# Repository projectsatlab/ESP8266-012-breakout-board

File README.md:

ESP8266-012F breakout board for sensors and probes devices

Coming soon...

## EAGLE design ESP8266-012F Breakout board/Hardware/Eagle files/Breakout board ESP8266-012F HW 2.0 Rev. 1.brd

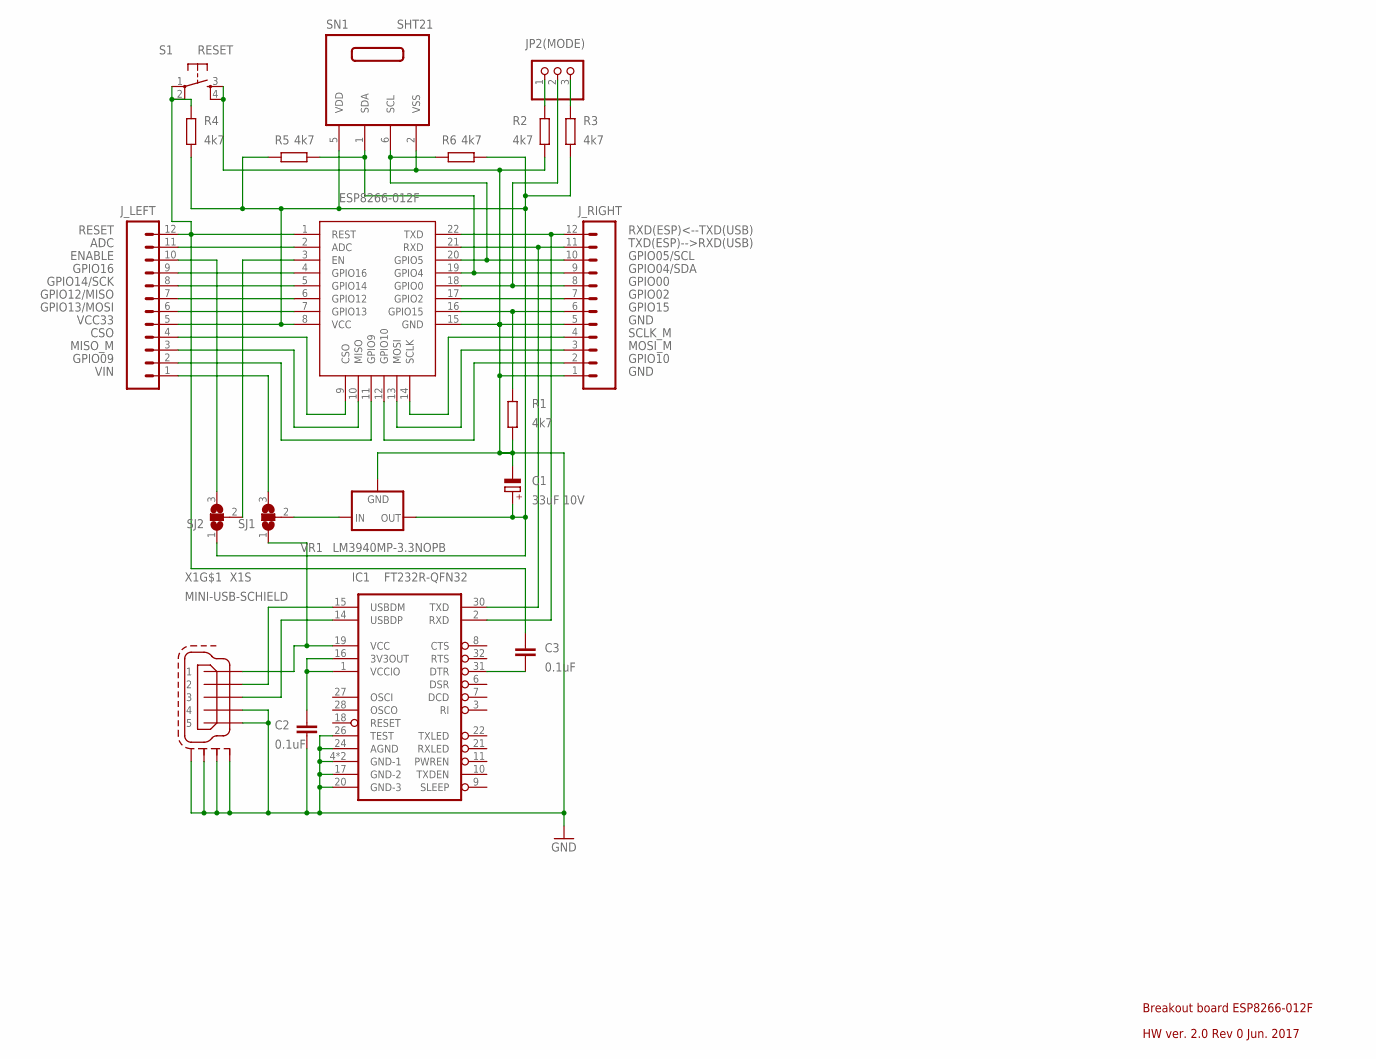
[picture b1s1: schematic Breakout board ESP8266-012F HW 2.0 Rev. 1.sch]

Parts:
C1: 33uF 10V; UD-5X5,8_NICHICON
C2, C3: 0.1uF; C0805
IC1: FT232R-QFN32; QFN32
JP2(MODE): PINHD-1X3; 1X03
J_LEFT: M12LONGPADS; 1X12_LONGPADS
J_RIGHT: M12LONGPADS; 1X12_LONGPADS
MDL1: ESP8266-012F; ESP8266-ESP12
R1, R2, R3, R4, R5, R6: 4k7; R0805
S1: RESET; C&K_KMS
SJ1, SJ2: SJ2W; SJ_2
SN1: SHT21; DFN6/SHT
VR1: LM3940MP-3.3NOPB; SOT223
X1: MINI-USB-SCHIELD; MOLEX_67503-X20

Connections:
ADC: J_LEFT.11, MDL1.2 (ADC)
CSO: J_LEFT.4, MDL1.9 (CSO)
D+: IC1.14 (USBDP), X1.3
D-: IC1.15 (USBDM), X1.2
ENABLE: J_LEFT.10, SJ2.3
GND: C1.-, C2.2, IC1.4 (GND-1), IC1.17 (GND-2), IC1.20 (GND-3), IC1.24 (AGND), IC1.26 (TEST), IC1.EXP (GND-1), J_RIGHT.1, J_RIGHT.5, MDL1.15 (GND), R1.2, R2.2, S1.3, S1.4, SN1.2 (VSS), VR1.2 (GND), VR1.4 (GND), X1.4, X1.5, X1.M1 (S1), X1.M2 (S2), X1.M3 (S3), X1.M4 (S4)
GPIO00: JP2(MODE).2, J_RIGHT.8, MDL1.18 (GPIO0)
GPIO02: J_RIGHT.7, MDL1.17 (GPIO2)
GPIO04/SDA: J_RIGHT.9, MDL1.19 (GPIO4), R5.2, SN1.1 (SDA)
GPIO05/SCL: J_RIGHT.10, MDL1.20 (GPIO5), R6.1, SN1.6 (SCL)
GPIO09: J_LEFT.2, MDL1.11 (GPIO9)
GPIO10: J_RIGHT.2, MDL1.12 (GPIO10)
GPIO12/MISO: J_LEFT.7, MDL1.6 (GPIO12)
GPIO13/MOSI: J_LEFT.6, MDL1.7 (GPIO13)
GPIO14/SCK: J_LEFT.8, MDL1.5 (GPIO14)
GPIO15: J_RIGHT.6, MDL1.16 (GPIO15), R1.1
GPIO16: J_LEFT.9, MDL1.4 (GPIO16)
MISO_M: J_LEFT.3, MDL1.10 (MISO)
MOSI_M: J_RIGHT.3, MDL1.13 (MOSI)
unnamed: SJ1.2, VR1.1 (IN)
unnamed: C3.2, IC1.31 (DTR)
unnamed: MDL1.3 (EN), SJ2.2
unnamed: C2.1, IC1.1 (VCCIO), IC1.16 (3V3OUT)
unnamed: JP2(MODE).3, R3.1
unnamed: JP2(MODE).1, R2.1
RESET: C3.1, J_LEFT.12, MDL1.1 (REST), R4.1, S1.1, S1.2
RXD(ESP)<--TXD(USB): IC1.2 (RXD), J_RIGHT.12, MDL1.22 (TXD)
SCLK_M: J_RIGHT.4, MDL1.14 (SCLK)
TXD(ESP)-->RXD(USB): IC1.30 (TXD), J_RIGHT.11, MDL1.21 (RXD)
VBUS: IC1.19 (VCC), SJ1.1, X1.1
VCC33: C1.+, J_LEFT.5, MDL1.8 (VCC), R3.2, R4.2, R5.1, R6.2, SJ2.1, SN1.5 (VDD), VR1.3 (OUT)
VIN: J_LEFT.1, SJ1.3

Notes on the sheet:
Breakout board ESP8266-012F
HW ver. 2.0 Rev 0 Jun. 2017

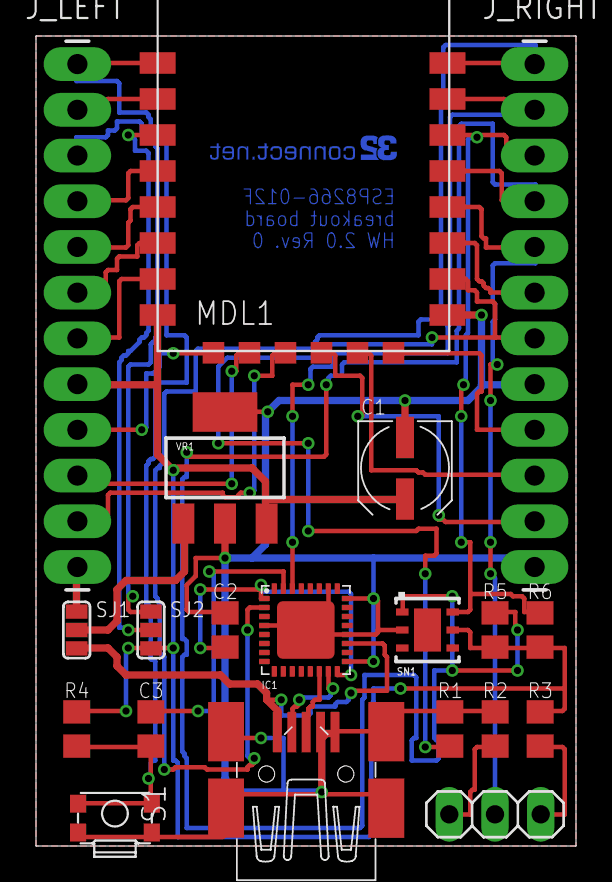
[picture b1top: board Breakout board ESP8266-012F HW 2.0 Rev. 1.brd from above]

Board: 2 copper layers, 30.0 x 45.0 mm, 20 parts (0 on the bottom side), 32 nets.

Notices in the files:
parts and their libraries:
SparkFun-Connectors: Licensing: Creative Commons ShareAlike 4.0 International - https://creativecommons.org/licenses/by-sa/4.0
sensirion: Copyright (C) 2011, Bob Starr
